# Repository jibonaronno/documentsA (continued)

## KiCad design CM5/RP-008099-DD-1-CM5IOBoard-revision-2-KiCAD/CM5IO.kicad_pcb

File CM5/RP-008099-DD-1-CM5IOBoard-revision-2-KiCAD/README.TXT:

These files have been created in version 9 of KiCAD.

Some of the 3d models need to be downloaded form the following places and put into the CM5IO.3shapes directory some models are approximations.

https://datasheets.raspberrypi.org/cm5/CM5-step.zip
https://www.molex.com/molex/products/part-detail/memory_card_socket/5033981892

The models provided in the 3dmodels directory are from various manufacturers including Diodes, Hirose, MTCONN, Toby, TRXCOM. Terms and conditions for the use of the models remain with the original manufacture.

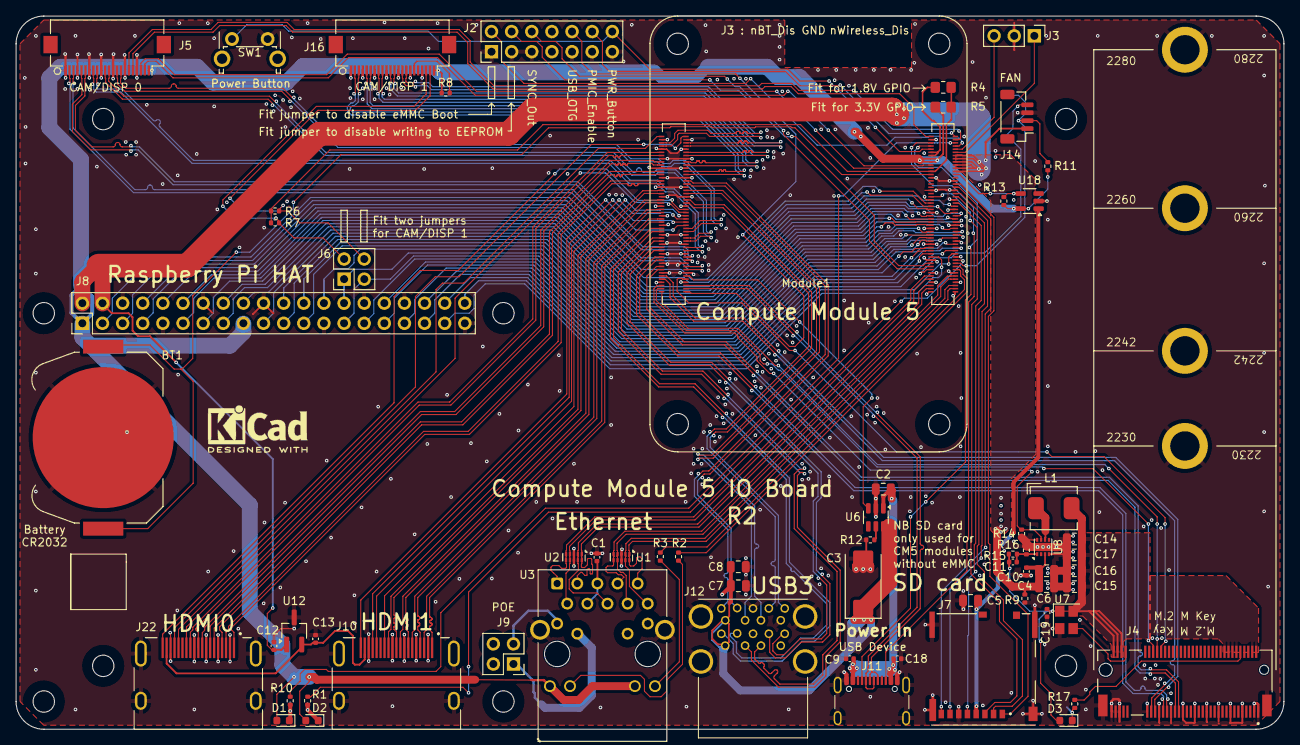
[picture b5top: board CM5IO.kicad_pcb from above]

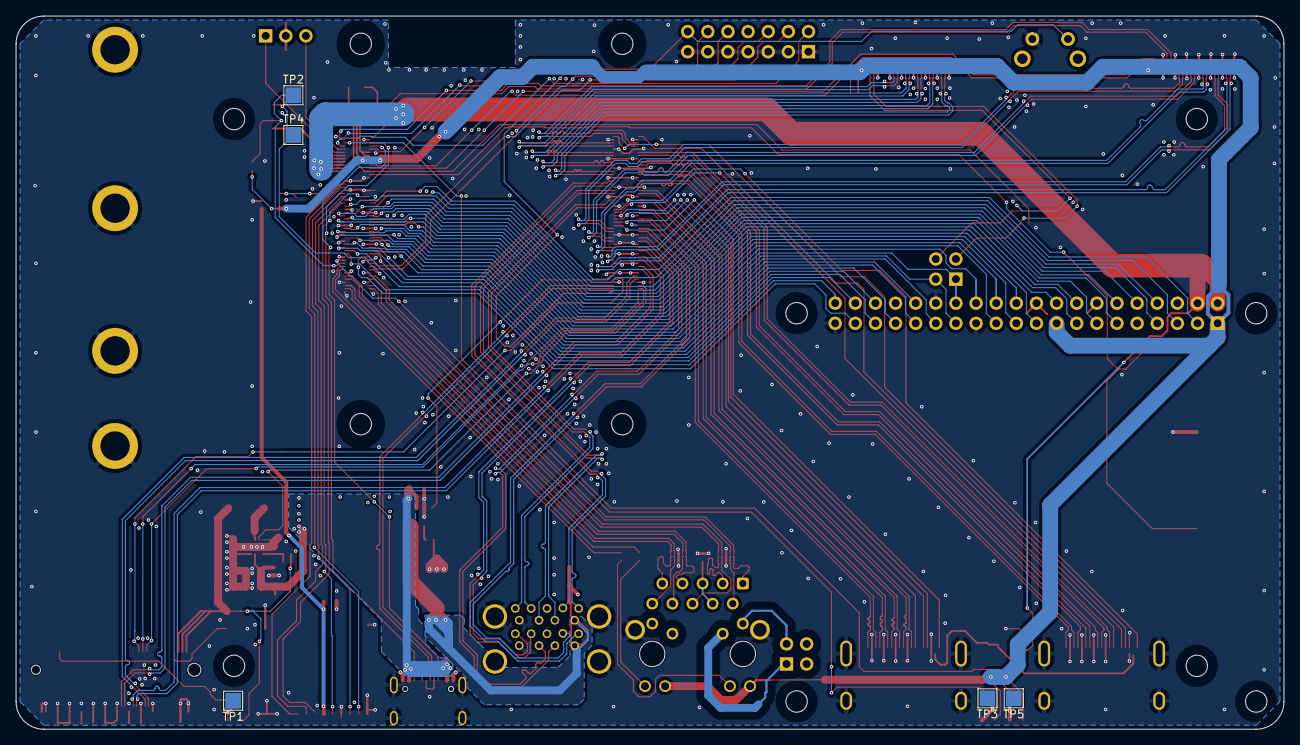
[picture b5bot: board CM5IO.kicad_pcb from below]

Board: 4 copper layers, 160.0 x 90.0 mm, 78 parts (5 on the bottom side), 160 nets.

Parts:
BT1: Battery_Cell; BatteryHolder_Keystone_3034_1x20mm
C1, C9, C10, C12, C13, C18, C19: 100n; C_0402_1005Metric
C2, C4, C5, C6, C7, C8, C14, C15, C16, C17: 10u; C_0805_2012Metric
C3: 100uF; CP_EIA-7343-31_Kemet-D
C11: 4.7nF; C_0402_1005Metric
D1: LED Red; LED_0603_1608Metric
D2, D3: LED Green; LED_0603_1608Metric
H1, H2, H3, H4, H5, H6, H7, H8: MountingHole; MountingHole_2.7mm_M2.5_DIN965
J2: Conn_02x07_Odd_Even; PinHeader_2x07_P2.54mm_Vertical
J3: Conn_01x03; PinHeader_1x03_P2.54mm_Vertical
J4: Bus_M.2_Socket_M; M.2 M Key socket
J5, J16: Conn_01x22_Female; Hirose_FH12-22S-0.5SH_1x22-1MP_P0.50mm_Horizontal
J6, J9: THD-02-R; PinHeader_2x02_P2.54mm_Vertical
J7: Micro_SD_Card_Det; SDCARD_MOLEX_503398-1892
J8: THD-20-R; PinHeader_2x20_P2.54mm_Vertical
J10, J22: 690-019-298-412; EDAC 690-019-298-412
J11: USB_C_Receptacle_USB2.0; USB_C_Receptacle_GCT_USB4105-xx-A_16P_TopMnt_Horizontal
J12: USB3_A; MTCONN_UBAF30-D2011
J14: JST_SHBM04B-SRSS-TB; JST_SH_BM04B-SRSS-TB_1x04-1MP_P1.00mm_Vertical
L1: 2.2uH; L_Bourns_SRP5030CC
Module1: ComputeModule5-CM5; Raspberry-Pi-5-Compute-Module
R1, R10, R17: 1k; R_0402_1005Metric
R2, R3: 470R; R_0402_1005Metric
R4: nf; R_0805_2012Metric_Pad1.20x1.40mm_HandSolder
R5: 0R; R_0805_2012Metric_Pad1.20x1.40mm_HandSolder
R6, R7, R8, R9, R16: 2.2K 1%; R_0402_1005Metric
R11, R13, R15: 10K 1%; R_0402_1005Metric
R12: 15K 1%; R_0402_1005Metric
R14: 100K 1%; R_0402_1005Metric
SW1: Right angle Tact button; SW_Tactile_SPST_Angled_PTS645Vx58-2LFS
TP1, TP2, TP3, TP4, TP5: TestPoint; TestPoint_Pad_2.0x2.0mm
U1, U2: TPD4EUSB30; USON-10_2.5x1.0mm_P0.5mm
U3: MagJack-A70-112-331N126; TRJG0926HENL
U6: AP22653W6; SOT-23-6
U7: ASEK-32.768KHZ-L-R-T; Crystal_SMD_3225-4Pin_3.2x2.5mm
U8: AP3441SHE-7B; DFN-8-1EP_2x2mm_P0.5mm_EP1.05x1.75mm
U12: RT9742SNGV; TSOT-23_HandSoldering
U18: RT9742GGJ5; SOT-23-5

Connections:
/+3.3v: D1.2 (A), D2.2 (A), J5.22, J8.1, J8.17, J16.22, Module1.84 (+3.3v_(Output)), Module1.86 (+3.3v_(Output)), R5.1, R8.1, R11.1, R13.1, U3.15 (LEDY_A), U3.17 (LEDG_A), U18.5 (IN)
/+5v: C2.1, C4.1, C6.1, C9.1, C10.1, C12.1, C18.1, J8.2, J8.4, J11.A4 (VBUS), J11.A9 (VBUS), J11.B4 (VBUS), J11.B9 (VBUS), J14.1, Module1.77 (+5v_(Input)), Module1.79 (+5v_(Input)), Module1.81 (+5v_(Input)), Module1.83 (+5v_(Input)), Module1.85 (+5v_(Input)), Module1.87 (+5v_(Input)), R9.1, U6.1 (IN), U8.3 (VIN), U12.1 (IN)
/CC1: J11.A5 (CC1), Module1.94 (CC1)
/CC2: J11.B5 (CC2), Module1.96 (CC2)
/CM5_GPIO ( Ethernet, GPIO, SDCARD)/+1.8v: Module1.88 (+1.8v_(Output)), Module1.90 (+1.8v_(Output)), R4.1
/CM5_GPIO ( Ethernet, GPIO, SDCARD)/BT_nDis: J3.3, Module1.91 (BT_nDisable)
/CM5_GPIO ( Ethernet, GPIO, SDCARD)/CAM_GPIO0: J5.17, Module1.97 (CAM_GPIO0)
/CM5_GPIO ( Ethernet, GPIO, SDCARD)/CAM_GPIO1: J5.18, Module1.100 (CAM_GPIO1)
/CM5_GPIO ( Ethernet, GPIO, SDCARD)/EEPROM_nWP: J2.4, Module1.20 (EEPROM_nWP)
/CM5_GPIO ( Ethernet, GPIO, SDCARD)/ETH_LEDG: Module1.17 (Ethernet_nLED2(3.3v)), R2.2
/CM5_GPIO ( Ethernet, GPIO, SDCARD)/ETH_LEDY: Module1.15 (Ethernet_nLED3(3.3v)), R3.2
/CM5_GPIO ( Ethernet, GPIO, SDCARD)/GPIO2: J8.3, Module1.58 (GPIO2)
/CM5_GPIO ( Ethernet, GPIO, SDCARD)/GPIO3: J8.5, Module1.56 (GPIO3)
/CM5_GPIO ( Ethernet, GPIO, SDCARD)/GPIO4: J8.7, Module1.54 (GPIO4)
/CM5_GPIO ( Ethernet, GPIO, SDCARD)/GPIO5: J8.29, Module1.34 (GPIO5)
/CM5_GPIO ( Ethernet, GPIO, SDCARD)/GPIO6: J8.31, Module1.30 (GPIO6)
/CM5_GPIO ( Ethernet, GPIO, SDCARD)/GPIO7: J8.26, Module1.37 (GPIO7)
/CM5_GPIO ( Ethernet, GPIO, SDCARD)/GPIO8: J8.24, Module1.39 (GPIO8)
/CM5_GPIO ( Ethernet, GPIO, SDCARD)/GPIO9: J8.21, Module1.40 (GPIO9)
/CM5_GPIO ( Ethernet, GPIO, SDCARD)/GPIO10: J8.19, Module1.44 (GPIO10)
/CM5_GPIO ( Ethernet, GPIO, SDCARD)/GPIO11: J8.23, Module1.38 (GPIO11)
/CM5_GPIO ( Ethernet, GPIO, SDCARD)/GPIO12: J8.32, Module1.31 (GPIO12)
/CM5_GPIO ( Ethernet, GPIO, SDCARD)/GPIO13: J8.33, Module1.28 (GPIO13)
/CM5_GPIO ( Ethernet, GPIO, SDCARD)/GPIO14: J8.8, Module1.55 (GPIO14)
/CM5_GPIO ( Ethernet, GPIO, SDCARD)/GPIO15: J8.10, Module1.51 (GPIO15)
/CM5_GPIO ( Ethernet, GPIO, SDCARD)/GPIO16: J8.36, Module1.29 (GPIO16)
/CM5_GPIO ( Ethernet, GPIO, SDCARD)/GPIO17: J8.11, Module1.50 (GPIO17)
/CM5_GPIO ( Ethernet, GPIO, SDCARD)/GPIO18: J8.12, Module1.49 (GPIO18)
/CM5_GPIO ( Ethernet, GPIO, SDCARD)/GPIO19: J8.35, Module1.26 (GPIO19)
/CM5_GPIO ( Ethernet, GPIO, SDCARD)/GPIO20: J8.38, Module1.27 (GPIO20)
/CM5_GPIO ( Ethernet, GPIO, SDCARD)/GPIO21: J8.40, Module1.25 (GPIO21)
/CM5_GPIO ( Ethernet, GPIO, SDCARD)/GPIO22: J8.15, Module1.46 (GPIO22)
/CM5_GPIO ( Ethernet, GPIO, SDCARD)/GPIO23: J8.16, Module1.47 (GPIO23)
/CM5_GPIO ( Ethernet, GPIO, SDCARD)/GPIO24: J8.18, Module1.45 (GPIO24)
/CM5_GPIO ( Ethernet, GPIO, SDCARD)/GPIO25: J8.22, Module1.41 (GPIO25)
/CM5_GPIO ( Ethernet, GPIO, SDCARD)/GPIO26: J8.37, Module1.24 (GPIO26)
/CM5_GPIO ( Ethernet, GPIO, SDCARD)/GPIO27: J8.13, Module1.48 (GPIO27)
/CM5_GPIO ( Ethernet, GPIO, SDCARD)/GPIO_VREF: Module1.78 (GPIO_VREF(1.8v/3.3v_Input)), R4.2, R5.2, R6.1, R7.1
/CM5_GPIO ( Ethernet, GPIO, SDCARD)/ID_SC: J6.1, J8.28, Module1.35 (ID_SC)
/CM5_GPIO ( Ethernet, GPIO, SDCARD)/ID_SD: J6.3, J8.27, Module1.36 (ID_SD)
/CM5_GPIO ( Ethernet, GPIO, SDCARD)/PMIC_ENABLE: J2.12, Module1.99 (PMIC_ENABLE)
/CM5_GPIO ( Ethernet, GPIO, SDCARD)/PWM: J14.2, Module1.19 (FAN_PWM), R11.2, TP2.1
/CM5_GPIO ( Ethernet, GPIO, SDCARD)/PWR_BUT: J2.14, Module1.92 (PWR_BUT), SW1.1
/CM5_GPIO ( Ethernet, GPIO, SDCARD)/SD_CLK: J7.5 (CLK), Module1.57 (SD_CLK)
/CM5_GPIO ( Ethernet, GPIO, SDCARD)/SD_CMD: J7.3 (CMD), Module1.62 (SD_CMD)
/CM5_GPIO ( Ethernet, GPIO, SDCARD)/SD_DAT0: J7.7 (DAT0), Module1.63 (SD_DAT0)
/CM5_GPIO ( Ethernet, GPIO, SDCARD)/SD_DAT1: J7.8 (DAT1), Module1.67 (SD_DAT1)
/CM5_GPIO ( Ethernet, GPIO, SDCARD)/SD_DAT2: J7.1 (DAT2), Module1.69 (SD_DAT2)
/CM5_GPIO ( Ethernet, GPIO, SDCARD)/SD_DAT3: J7.2 (DAT3/CD), Module1.61 (SD_DAT3)
/CM5_GPIO ( Ethernet, GPIO, SDCARD)/SD_PWR: C5.1, J7.4 (VDD), U18.1 (OUT)
/CM5_GPIO ( Ethernet, GPIO, SDCARD)/SD_PWR_ON: Module1.75 (SD_PWR_ON), R13.2, U18.4 (EN)
/CM5_GPIO ( Ethernet, GPIO, SDCARD)/SYNC_OUT: J2.6, Module1.18 (Ethernet_SYNC_OUT(3.3v))
/CM5_GPIO ( Ethernet, GPIO, SDCARD)/TACHO: J14.4, Module1.16 (FAN_TACHO), TP4.1
/CM5_GPIO ( Ethernet, GPIO, SDCARD)/TR0_TAP: J9.3, U3.11 (VC1)
/CM5_GPIO ( Ethernet, GPIO, SDCARD)/TR1_TAP: J9.1, U3.12 (VC2)
/CM5_GPIO ( Ethernet, GPIO, SDCARD)/TR2_TAP: J9.2, U3.13 (VC3)
/CM5_GPIO ( Ethernet, GPIO, SDCARD)/TR3_TAP: J9.4, U3.14 (VC4)
/CM5_GPIO ( Ethernet, GPIO, SDCARD)/TRD0_N: Module1.10 (Ethernet_Pair0_N), U2.4 (D2+), U2.7, U3.2 (TRD0-)
/CM5_GPIO ( Ethernet, GPIO, SDCARD)/TRD0_P: Module1.12 (Ethernet_Pair0_P), U2.5 (D2-), U2.6, U3.1 (TRD0+)
/CM5_GPIO ( Ethernet, GPIO, SDCARD)/TRD1_N: Module1.6 (Ethernet_Pair1_N), U2.2 (D1-), U2.9, U3.6 (TRD1-)
/CM5_GPIO ( Ethernet, GPIO, SDCARD)/TRD1_P: Module1.4 (Ethernet_Pair1_P), U2.1 (D1+), U2.10, U3.3 (TRD1+)
/CM5_GPIO ( Ethernet, GPIO, SDCARD)/TRD2_N: Module1.9 (Ethernet_Pair2_N), U1.4 (D2+), U1.7, U3.8 (TRD2-)
/CM5_GPIO ( Ethernet, GPIO, SDCARD)/TRD2_P: Module1.11 (Ethernet_Pair2_P), U1.5 (D2-), U1.6, U3.7 (TRD2+)
/CM5_GPIO ( Ethernet, GPIO, SDCARD)/TRD3_N: Module1.5 (Ethernet_Pair3_N), U1.2 (D1-), U1.9, U3.10 (TRD3-)
/CM5_GPIO ( Ethernet, GPIO, SDCARD)/TRD3_P: Module1.3 (Ethernet_Pair3_P), U1.1 (D1+), U1.10, U3.9 (TRD3+)
/CM5_GPIO ( Ethernet, GPIO, SDCARD)/USBOTG: J2.10, Module1.101 (USB_OTG_ID)
/CM5_GPIO ( Ethernet, GPIO, SDCARD)/VBAT: BT1.1 (+), Module1.76 (VBAT)
/CM5_GPIO ( Ethernet, GPIO, SDCARD)/WL_nDis: J3.1, Module1.89 (WiFi_nDisable)
/CM5_GPIO ( Ethernet, GPIO, SDCARD)/nPWR_LED: Module1.95 (LED_nPWR), R10.2
/CM5_GPIO ( Ethernet, GPIO, SDCARD)/nRPIBOOT: J2.2, Module1.93 (nRPIBOOT)
/CM5_HighSpeed/DPHY0_C_N: J5.8, Module1.127 (MIPI0_C_N)
/CM5_HighSpeed/DPHY0_C_P: J5.9, Module1.129 (MIPI0_C_P)
/CM5_HighSpeed/DPHY0_D0_N: J5.2, Module1.115 (MIPI0_D0_N)
/CM5_HighSpeed/DPHY0_D0_P: J5.3, Module1.117 (MIPI0_D0_P)
/CM5_HighSpeed/DPHY0_D1_N: J5.5, Module1.121 (MIPI0_D1_N)
/CM5_HighSpeed/DPHY0_D1_P: J5.6, Module1.123 (MIPI0_D1_P)
/CM5_HighSpeed/DPHY0_D2_N: J5.11, Module1.133 (MIPI0_D2_N)
/CM5_HighSpeed/DPHY0_D2_P: J5.12, Module1.135 (MIPI0_D2_P)
/CM5_HighSpeed/DPHY0_D3_N: J5.14, Module1.139 (MIPI0_D3_N)
/CM5_HighSpeed/DPHY0_D3_P: J5.15, Module1.141 (MIPI0_D3_P)
/CM5_HighSpeed/DPHY1_C_N: J16.8, Module1.187 (MIPI1_C_N)
/CM5_HighSpeed/DPHY1_C_P: J16.9, Module1.189 (MIPI1_C_P)
/CM5_HighSpeed/DPHY1_D0_N: J16.2, Module1.175 (MIPI1_D0_N)
/CM5_HighSpeed/DPHY1_D0_P: J16.3, Module1.177 (MIPI1_D0_P)
/CM5_HighSpeed/DPHY1_D1_N: J16.5, Module1.181 (MIPI1_D1_N)
/CM5_HighSpeed/DPHY1_D1_P: J16.6, Module1.183 (MIPI1_D1_P)
/CM5_HighSpeed/DPHY1_D2_N: J16.11, Module1.193 (MIPI1_D2_N)
/CM5_HighSpeed/DPHY1_D2_P: J16.12, Module1.195 (MIPI1_D2_P)
/CM5_HighSpeed/DPHY1_D3_N: J16.14, Module1.194 (MIPI1_D3_N)
/CM5_HighSpeed/DPHY1_D3_P: J16.15, Module1.196 (MIPI1_D3_P)
/CM5_HighSpeed/HDMI0_CEC: J22.13 (CEC), Module1.151 (HDMI0_CEC)
/CM5_HighSpeed/HDMI0_CK_N: J22.12 (CK-), Module1.190 (HDMI0_CLK_N)
/CM5_HighSpeed/HDMI0_CK_P: J22.10 (CK+), Module1.188 (HDMI0_CLK_P)
/CM5_HighSpeed/HDMI0_D0_N: J22.9 (D0-), Module1.184 (HDMI0_TX0_N)
/CM5_HighSpeed/HDMI0_D0_P: J22.7 (D0+), Module1.182 (HDMI0_TX0_P)
/CM5_HighSpeed/HDMI0_D1_N: J22.6 (D1-), Module1.178 (HDMI0_TX1_N)
/CM5_HighSpeed/HDMI0_D1_P: J22.4 (D1+), Module1.176 (HDMI0_TX1_P)
/CM5_HighSpeed/HDMI0_D2_N: J22.3 (D2-), Module1.172 (HDMI0_TX2_N)
/CM5_HighSpeed/HDMI0_D2_P: J22.1 (D2+), Module1.170 (HDMI0_TX2_P)
/CM5_HighSpeed/HDMI0_HOTPLUG: J22.19 (HPD/HEAC-), Module1.153 (HDMI0_HOTPLUG)
/CM5_HighSpeed/HDMI0_SCL: J22.15 (SCL), Module1.200 (HDMI0_SCL)
/CM5_HighSpeed/HDMI0_SDA: J22.16 (SDA), Module1.199 (HDMI0_SDA)
/CM5_HighSpeed/HDMI1_CEC: J10.13 (CEC), Module1.149 (HDMI1_CEC)
/CM5_HighSpeed/HDMI1_CK_N: J10.12 (CK-), Module1.166 (HDMI1_CLK_N)
/CM5_HighSpeed/HDMI1_CK_P: J10.10 (CK+), Module1.164 (HDMI1_CLK_P)
/CM5_HighSpeed/HDMI1_D0_N: J10.9 (D0-), Module1.160 (HDMI1_TX0_N)
/CM5_HighSpeed/HDMI1_D0_P: J10.7 (D0+), Module1.158 (HDMI1_TX0_P)
/CM5_HighSpeed/HDMI1_D1_N: J10.6 (D1-), Module1.154 (HDMI1_TX1_N)
/CM5_HighSpeed/HDMI1_D1_P: J10.4 (D1+), Module1.152 (HDMI1_TX1_P)
/CM5_HighSpeed/HDMI1_D2_N: J10.3 (D2-), Module1.148 (HDMI1_TX2_N)
/CM5_HighSpeed/HDMI1_D2_P: J10.1 (D2+), Module1.146 (HDMI1_TX2_P)
/CM5_HighSpeed/HDMI1_HOTPLUG: J10.19 (HPD/HEAC-), Module1.143 (HDMI1_HOTPLUG)
/CM5_HighSpeed/HDMI1_SCL: J10.15 (SCL), Module1.147 (HDMI1_SCL)
/CM5_HighSpeed/HDMI1_SDA: J10.16 (SDA), Module1.145 (HDMI1_SDA)
/CM5_HighSpeed/HDMI_5v: C13.1, J10.18 (+5V), J22.18 (+5V), U12.2 (OUT)
/CM5_HighSpeed/PCIE_CLK_N: J4.53 (REFCLKn), Module1.112 (PCIe_CLK_N)
/CM5_HighSpeed/PCIE_CLK_P: J4.55 (REFCLKp), Module1.110 (PCIe_CLK_P)
/CM5_HighSpeed/PCIE_PWR_EN: Module1.106 (PCIE_PWR_EN), R14.1, U8.7 (EN)
/CM5_HighSpeed/PCIE_RX_N: J4.43 (PETp0), Module1.118 (PCIe_RX_N)
/CM5_HighSpeed/PCIE_RX_P: J4.41 (PETn0), Module1.116 (PCIe_RX_P)
/CM5_HighSpeed/PCIE_TX_N: J4.49 (PERp0), Module1.124 (PCIe_TX_N)
/CM5_HighSpeed/PCIE_TX_P: J4.47 (PERn0), Module1.122 (PCIe_TX_P)
/CM5_HighSpeed/PCIE_nCLKREQ: J4.52 (~CLKREQ), Module1.102 (PCIe_nCLKREQ)
/CM5_HighSpeed/PCIE_nRST: J4.50 (~PERST), Module1.109 (PCIe_nRST)
/CM5_HighSpeed/PCIE_nWAKE: J4.54 (~PEWAKE), Module1.104 (PCIE_nWAKE)
/CM5_HighSpeed/SCL0: J5.20, Module1.80 (SCL0)
/CM5_HighSpeed/SCL1: J6.2, J16.20, R7.2
/CM5_HighSpeed/SDA0: J5.21, Module1.82 (SDA0)
/CM5_HighSpeed/SDA1: J6.4, J16.21, R6.2
/CM5_HighSpeed/USB3-0-D_N: J12.A2 (D-), Module1.136 (USB3-0-D_N)
/CM5_HighSpeed/USB3-0-D_P: J12.A3 (D+), Module1.134 (USB3-0-D_P)
/CM5_HighSpeed/USB3-0-RX_N: J12.A6 (SSRX+), Module1.128 (USB3-0-RX_N)
/CM5_HighSpeed/USB3-0-RX_P: J12.A5 (SSRX-), Module1.130 (USB3-0-RX_P)
/CM5_HighSpeed/USB3-0-TX_N: J12.A9 (SSTX+), Module1.140 (USB3-0-TX_N)
/CM5_HighSpeed/USB3-0-TX_P: J12.A8 (SSTX-), Module1.142 (USB3-0-TX_P)
/CM5_HighSpeed/USB3-1-D_N: J12.B2 (D-), Module1.165 (USB3-1-D_N)
/CM5_HighSpeed/USB3-1-D_P: J12.B3 (D+), Module1.163 (USB3-1-D_P)
/CM5_HighSpeed/USB3-1-RX_N: J12.B6 (SSRX+), Module1.157 (USB3-1-RX_N)
/CM5_HighSpeed/USB3-1-RX_P: J12.B5 (SSRX-), Module1.159 (USB3-1-RX_P)
/CM5_HighSpeed/USB3-1-TX_N: J12.B9 (SSTX+), Module1.169 (USB3-1-TX_N)
/CM5_HighSpeed/USB3-1-TX_P: J12.B8 (SSTX-), Module1.171 (USB3-1-TX_P)
/CM5_HighSpeed/VBUS: C3.1, C7.1, C8.1, J12.A1 (VBUS), J12.B1 (VBUS), U6.6 (OUT)
/CM5_HighSpeed/VBUS_EN: Module1.111 (VBUS_EN), U6.3 (EN)
/PCIe-M2/FB: C11.2, R15.2, R16.1, U8.1 (FB)
/PCIe-M2/M2_3v3: C11.1, C14.1, C15.1, C16.1, C17.1, C19.1, D3.2 (A), J4.2 (3.3V), J4.4 (3.3V), J4.12 (3.3V), J4.14 (3.3V), J4.16 (3.3V), J4.18 (3.3V), J4.70 (3.3V), J4.72 (3.3V), J4.74 (3.3V), L1.2, R15.1, U7.1 (EN), U7.4 (VDD)
/USB2_N: J11.A7 (D-), J11.B7 (D-), Module1.103 (USB2_N)
/USB2_P: J11.A6 (D+), J11.B6 (D+), Module1.105 (USB2_P)
GND: BT1.2 (-), C1.2, C2.2, C3.2, C4.2, C5.2, C6.2, C7.2, C8.2, C9.2, C10.2, C12.2, C13.2, C14.2, C15.2, C16.2, C17.2, C18.2, C19.2, J2.1, J2.3, J2.5, J2.7, J2.9, J2.11, J2.13, J3.2, J4.1 (GND), J4.3 (GND), J4.9 (GND), J4.15 (GND), J4.21 (GND), J4.27 (GND), J4.33 (GND), J4.39 (GND), J4.45 (GND), J4.51 (GND), J4.57 (GND), J4.71 (GND), J4.73 (GND), J4.75 (GND), J4.M1 (GND2230), J4.M2 (GND2242), J4.M3 (GND2260), J4.M4 (GND2280), J4.S1, J4.S2, J5.1, J5.4, J5.7, J5.10, J5.13, J5.16, J5.19, J7.6 (VSS), J7.11 (SHIELD), J8.6, J8.9, J8.14, J8.20, J8.25, J8.30, J8.34, J8.39, J10.2 (D2S), J10.5 (D1S), J10.8 (D0S), J10.11 (CKS), J10.17 (GND), J10.SH1 (SH), J10.SH2 (SH), J10.SH3 (SH), J10.SH4 (SH), J11.A1 (GND), J11.A12 (GND), J11.B1 (GND), J11.B12 (GND), J11.S1 (SHIELD), J12.10 (SHIELD), J12.A4 (GND), J12.A7 (DRAIN), J12.B4 (GND), J12.B7 (DRAIN), J14.3, J16.1, J16.4, J16.7, J16.10, J16.13, J16.16, J16.19, J22.2 (D2S), J22.5 (D1S), J22.8 (D0S), J22.11 (CKS), J22.17 (GND), J22.SH1 (SH), J22.SH2 (SH), J22.SH3 (SH), J22.SH4 (SH), Module1.1 (GND), Module1.2 (GND), Module1.7 (GND), Module1.8 (GND), Module1.13 (GND), Module1.14 (GND), Module1.22 (GND), Module1.23 (GND), Module1.32 (GND), Module1.33 (GND), Module1.42 (GND), Module1.43 (GND), Module1.52 (GND), Module1.53 (GND), Module1.59 (GND), Module1.60 (GND), Module1.65 (GND), Module1.66 (GND), Module1.71 (GND), Module1.74 (GND), Module1.98 (GND), Module1.107 (GND), Module1.108 (GND), Module1.113 (GND), Module1.114 (GND), Module1.119 (GND), Module1.120 (GND), Module1.125 (GND), Module1.126 (GND), Module1.131 (GND), Module1.132 (GND), Module1.137 (GND), Module1.138 (GND), Module1.144 (GND), Module1.150 (GND), Module1.155 (GND), Module1.156 (GND), Module1.161 (GND), Module1.162 (GND), Module1.167 (GND), Module1.168 (GND), Module1.173 (GND), Module1.174 (GND), Module1.179 (GND), Module1.180 (GND), Module1.185 (GND), Module1.186 (GND), Module1.191 (GND), Module1.192 (GND), Module1.197 (GND), Module1.198 (GND), R9.2, R12.2, R14.2, R16.2, SW1.2, U1.3 (GND), U1.8 (GND), U2.3 (GND), U2.8 (GND), U3.19 (SHIELD), U3.20 (SHIELD), U6.2 (GND), U7.2 (GND), U8.4 (PGND), U8.8 (SGND), U8.9 (PAD), U12.3 (GND), U18.2 (GND)
unnamed: C1.1, U3.4 (CT), U3.5 (CT)
unnamed: D1.1 (K), R10.1, TP5.1
unnamed: D2.1 (K), R1.1, TP3.1
unnamed: D3.1 (K), R17.1, TP1.1
unnamed: J4.10 (DAS/~DSS/~LED1), R17.2
unnamed: J4.68 (SUSCLK), U7.3 (Out)
unnamed: J16.17, R8.2
unnamed: Module1.21 (LED_nACT), R1.2
unnamed: R3.1, U3.18 (LEDG_K)
unnamed: R2.1, U3.16 (LEDY_K)
unnamed: R12.1, U6.5 (ILIM)
unnamed: L1.1, U8.6 (LX)

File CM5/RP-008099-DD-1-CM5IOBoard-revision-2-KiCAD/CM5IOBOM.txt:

"Id";"Designator";"Footprint";"Quantity";"Designation";"Supplier and ref";
1;"BT1";"BatteryHolder_Keystone_3034_1x20mm";1;"Battery_Cell";;;
2;"SW1";"SW_Tactile_SPST_Angled_PTS645Vx39-2LFS";1;"Right angle Tact button";;;
3;"C1,C12,C13,C10,C18,C9,C19";"C_0402_1005Metric";7;"100n";;;
4;"C5,C6,C16,C8,C2,C17,C7,C15,C14,C4";"C_0805_2012Metric";10;"10u";;;
5;"J5,J16";"Hirose_FH12-22S-0.5SH_1x22-1MP_P0.50mm_Horizontal";2;"Conn_01x22_Female";;;
6;"R10,R1,R17";"R_0402_1005Metric";3;"1k";;;
7;"U1,U2";"USON-10_2.5x1.0mm_P0.5mm";2;"TPD4EUSB30";;;
8;"U12";"TSOT-23_HandSoldering";1;"RT9742SNGV";;;
9;"J8";"PinHeader_2x20_P2.54mm_Vertical";1;"THD-20-R";;;
10;"D2,D3";"LED_0603_1608Metric";2;"LED Green";;;
11;"R3,R2";"R_0402_1005Metric";2;"470R";;;
12;"J9,J6";"PinHeader_2x02_P2.54mm_Vertical";2;"THD-02-R";;;
13;"J11";"USB_C_Receptacle_GCT_USB4105-xx-A_16P_TopMnt_Horizontal";1;"USB_C_Receptacle_USB2.0";;;
14;"D1";"LED_0603_1608Metric";1;"LED Red";;;
15;"U5";"SOT-353_SC-70-5";1;"74LVC1G07SE-7";;;
16;"U18";"SOT-23-5";1;"RT9742GGJ5";;;
17;"U3";"TRJG0926HENL";1;"MagJack-A70-112-331N126";;;
18;"J10,J22";"EDAC 690-019-298-412";2;"690-019-298-412";;;
19;"R6,R7,R8,R16";"R_0402_1005Metric";4;"2.2K 1%";;;
20;"J2";"PinHeader_2x07_P2.54mm_Vertical";1;"Conn_02x07_Odd_Even";;;
21;"R5";"R_0805_2012Metric_Pad1.20x1.40mm_HandSolder";1;"0R";;;
22;"U8";"DFN-8-1EP_2x2mm_P0.5mm_EP1.05x1.75mm";1;"AP3441SHE-7B";;;
23;"J7";"SDCARD_MOLEX_503398-1892";1;"Micro_SD_Card_Det";;;
24;"J4";"M.2 M Key socket";1;"Bus_M.2_Socket_M";;;
25;"C11";"C_0402_1005Metric";1;"4.7nF";;;
26;"J12";"MTCONN_UBAF30-D2011";1;"USB3_A";;;
27;"J14";"JST_SH_BM04B-SRSS-TB_1x04-1MP_P1.00mm_Vertical";1;"JST_SHBM04B-SRSS-TB";;;
28;"C3";"CP_EIA-7343-31_Kemet-D";1;"100uF";;;
29;"U7";"Crystal_SMD_3225-4Pin_3.2x2.5mm";1;"ASEK-32.768KHZ-L-R-T";;;
30;"U6";"SOT-23-6";1;"AP22653W6";;;
31;"L1";"L_Bourns_SRP5030CC";1;"2.2uH";;;
32;"R15";"R_0402_1005Metric";1;"10K 1%";;;
33;"R12";"R_0402_1005Metric";1;"15K 1%";;;
34;"R14";"R_0402_1005Metric";1;"100K 1%";;;
35;"Module1";"Raspberry-Pi-5-Compute-Module";1;"ComputeModule5-CM5";;;

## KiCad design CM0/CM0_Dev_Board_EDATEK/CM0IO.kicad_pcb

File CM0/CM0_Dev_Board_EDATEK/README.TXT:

These files have been created in version 9 of KiCAD.

Some of the 3d models need to be downloaded form the following places and put into the CM4IO.3dshapes directory some models are approximations.

https://www.molex.com/molex/products/part-detail/memory_card_socket/5033981892
https://www.molex.com/en-us/products/part-detail/2086581051

The models provided in the 3dmodels directory are from various manufacturers including RaspberryPi, Hirose. Terms and conditions for the use of the models remain with the original manufacture.

The CM0 model has the following license :

= Disclaimer =
These 3D models are provided under the MIT license included at the end of this file. The 3D models may incorporate individual 3D models that have been provided by third parties with permission to redistribute. No additional license terms are imposed by this use of third party provided 3D models, where applicable.

The overall 3D model and any individual 3D models incorporated into the whole, whether created by first or a third party, are provided here for guidance only and without guarantee of accuracy. Additionally, provided 3D model data may not reflect the most current version(s). Any third party intending to use the provided 3D model for appearance and fitment purposes must refer to manufacturer information and conduct suitable measurements of the physical product.

= MIT License =
Copyright (c) 2025 Raspberry Pi Ltd

Permission is hereby granted, free of charge, to any person obtaining a copy of this software and associated documentation files (the "Software"), to deal in the Software without restriction, including without limitation the rights to use, copy, modify, merge, publish, distribute, sublicense, and/or sell copies of the Software, and to permit persons to whom the Software is furnished to do so, subject to the following conditions:

The above copyright notice and this permission notice shall be included in all copies or substantial portions of the Software.

THE SOFTWARE IS PROVIDED "AS IS", WITHOUT WARRANTY OF ANY KIND, EXPRESS OR IMPLIED, INCLUDING BUT NOT LIMITED TO THE WARRANTIES OF MERCHANTABILITY, FITNESS FOR A PARTICULAR PURPOSE AND NONINFRINGEMENT. IN NO EVENT SHALL THE AUTHORS OR COPYRIGHT HOLDERS BE LIABLE FOR ANY CLAIM, DAMAGES OR OTHER LIABILITY, WHETHER IN AN ACTION OF CONTRACT, TORT OR OTHERWISE, ARISING FROM, OUT OF OR IN CONNECTION WITH THE SOFTWARE OR THE USE OR OTHER DEALINGS IN THE SOFTWARE.

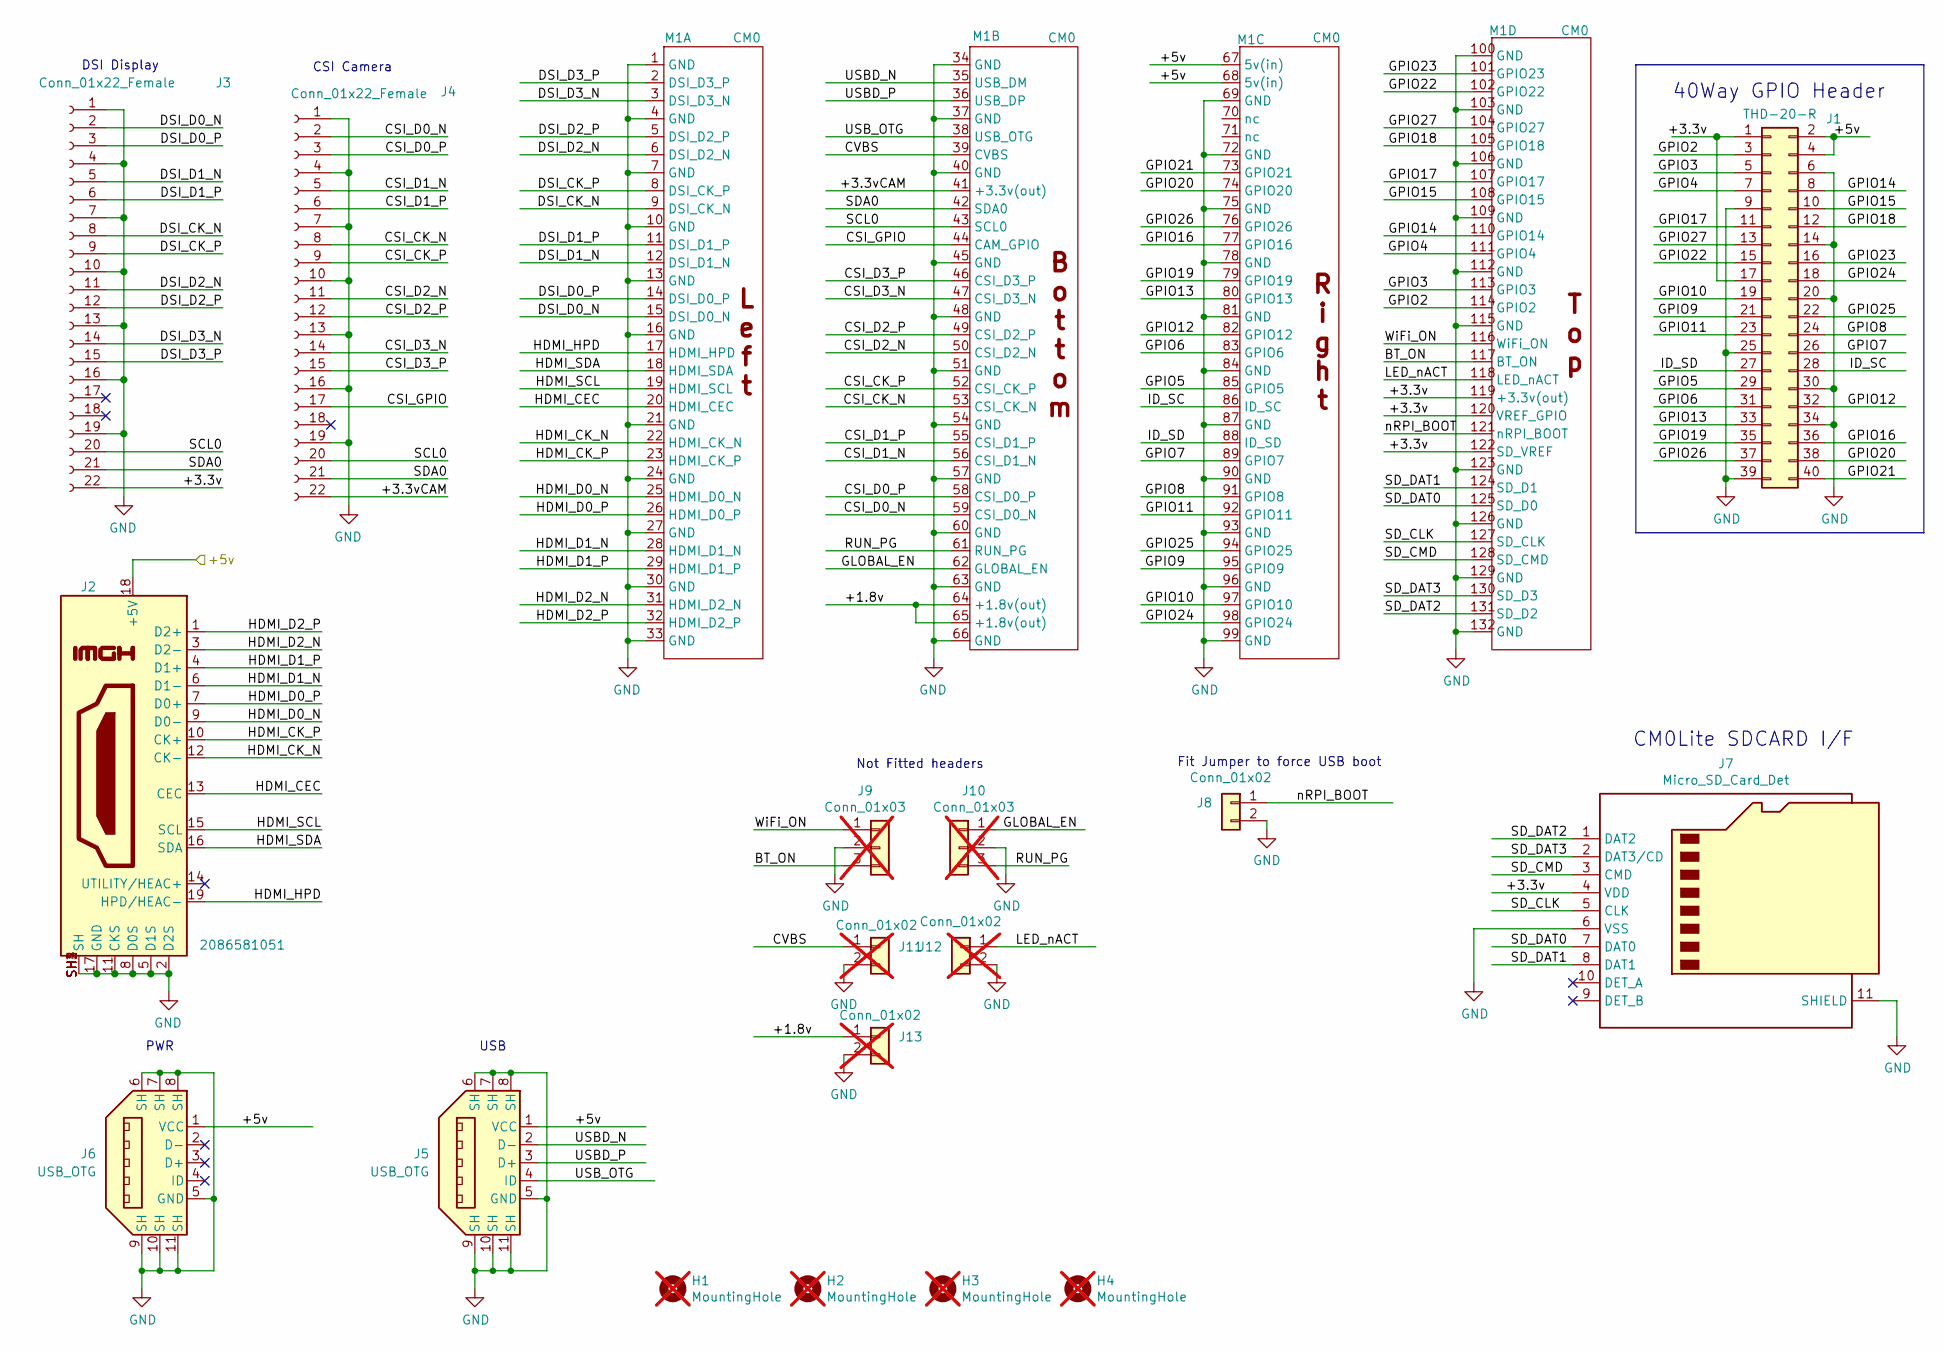
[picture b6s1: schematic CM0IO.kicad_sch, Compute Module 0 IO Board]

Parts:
H1, H2, H3, H4: MountingHole; MountingHole_2.7mm_M2.5; Part Description M2.5 mounting hole; not fitted
J1: THD-20-R; PinHeader_2x20_P2.54mm_Vertical; Part Description PinHeader_2x20_P2.54mm_Vertical
J2: 2086581051; Molex_2086581051; Part Description HDMI Connector, Right Angle, 19 Contact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
J3, J4: Conn_01x22_Female; Hirose_FH12-22S-0.5SH_1x22-1MP_P0.50mm_Horizontal; Part Description 22 Position FFC, FPC Connector Contacts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
J5, J6: USB_OTG; amphenol_10103594-0001lf; Part Description USB - micro B USB 2.0 Receptacle Connec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
J7: Micro_SD_Card_Det; SDCARD_MOLEX_503398-1892; Part Description 9 (8 + 1) Position Card Connector micro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
J8: Conn_01x02; PinHeader_1x02_P2.54mm_Vertical
J9, J10: Conn_01x03; PinHeader_1x03_P2.54mm_Vertical; Part Description 3pin 0.1" connector; not fitted
J11, J12, J13: Conn_01x02; PinHeader_1x02_P2.54mm_Vertical; not fitted
M1: CM0; Part Description Compute Module 0

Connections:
/+1.8v: J13.1, M1.64 (+1.8v(out)), M1.65 (+1.8v(out))
/+3.3v: J1.1, J1.17, J3.22, J7.4 (VDD), M1.119 (+3.3v(out)), M1.120 (VREF_GPIO), M1.122 (SD_VREF)
/+3.3vCAM: J4.22, M1.41 (+3.3v(out))
/+5v: J1.2, J1.4, J2.18 (+5V), J5.1 (VCC), J6.1 (VCC), M1.67 (5v(in)), M1.68 (5v(in))
/BT_ON: J9.3, M1.117 (BT_ON)
/CSI_CK_N: J4.8, M1.53 (CSI_CK_N)
/CSI_CK_P: J4.9, M1.52 (CSI_CK_P)
/CSI_D0_N: J4.2, M1.59 (CSI_D0_N)
/CSI_D0_P: J4.3, M1.58 (CSI_D0_P)
/CSI_D1_N: J4.5, M1.56 (CSI_D1_N)
/CSI_D1_P: J4.6, M1.55 (CSI_D1_P)
/CSI_D2_N: J4.11, M1.50 (CSI_D2_N)
/CSI_D2_P: J4.12, M1.49 (CSI_D2_P)
/CSI_D3_N: J4.14, M1.47 (CSI_D3_N)
/CSI_D3_P: J4.15, M1.46 (CSI_D3_P)
/CSI_GPIO: J4.17, M1.44 (CAM_GPIO)
/CVBS: J11.1, M1.39 (CVBS)
/DSI_CK_N: J3.8, M1.9 (DSI_CK_N)
/DSI_CK_P: J3.9, M1.8 (DSI_CK_P)
/DSI_D0_N: J3.2, M1.15 (DSI_D0_N)
/DSI_D0_P: J3.3, M1.14 (DSI_D0_P)
/DSI_D1_N: J3.5, M1.12 (DSI_D1_N)
/DSI_D1_P: J3.6, M1.11 (DSI_D1_P)
/DSI_D2_N: J3.11, M1.6 (DSI_D2_N)
/DSI_D2_P: J3.12, M1.5 (DSI_D2_P)
/DSI_D3_N: J3.14, M1.3 (DSI_D3_N)
/DSI_D3_P: J3.15, M1.2 (DSI_D3_P)
/GLOBAL_EN: J10.1, M1.62 (GLOBAL_EN)
/GPIO2: J1.3, M1.114 (GPIO2)
/GPIO3: J1.5, M1.113 (GPIO3)
/GPIO4: J1.7, M1.111 (GPIO4)
/GPIO5: J1.29, M1.85 (GPIO5)
/GPIO6: J1.31, M1.83 (GPIO6)
/GPIO7: J1.26, M1.89 (GPIO7)
/GPIO8: J1.24, M1.91 (GPIO8)
/GPIO9: J1.21, M1.95 (GPIO9)
/GPIO10: J1.19, M1.97 (GPIO10)
/GPIO11: J1.23, M1.92 (GPIO11)
/GPIO12: J1.32, M1.82 (GPIO12)
/GPIO13: J1.33, M1.80 (GPIO13)
/GPIO14: J1.8, M1.110 (GPIO14)
/GPIO15: J1.10, M1.108 (GPIO15)
/GPIO16: J1.36, M1.77 (GPIO16)
/GPIO17: J1.11, M1.107 (GPIO17)
/GPIO18: J1.12, M1.105 (GPIO18)
/GPIO19: J1.35, M1.79 (GPIO19)
/GPIO20: J1.38, M1.74 (GPIO20)
/GPIO21: J1.40, M1.73 (GPIO21)
/GPIO22: J1.15, M1.102 (GPIO22)
/GPIO23: J1.16, M1.101 (GPIO23)
/GPIO24: J1.18, M1.98 (GPIO24)
/GPIO25: J1.22, M1.94 (GPIO25)
/GPIO26: J1.37, M1.76 (GPIO26)
/GPIO27: J1.13, M1.104 (GPIO27)
/HDMI_CEC: J2.13 (CEC), M1.20 (HDMI_CEC)
/HDMI_CK_N: J2.12 (CK-), M1.22 (HDMI_CK_N)
/HDMI_CK_P: J2.10 (CK+), M1.23 (HDMI_CK_P)
/HDMI_D0_N: J2.9 (D0-), M1.25 (HDMI_D0_N)
/HDMI_D0_P: J2.7 (D0+), M1.26 (HDMI_D0_P)
/HDMI_D1_N: J2.6 (D1-), M1.28 (HDMI_D1_N)
/HDMI_D1_P: J2.4 (D1+), M1.29 (HDMI_D1_P)
/HDMI_D2_N: J2.3 (D2-), M1.31 (HDMI_D2_N)
/HDMI_D2_P: J2.1 (D2+), M1.32 (HDMI_D2_P)
/HDMI_HPD: J2.19 (HPD/HEAC-), M1.17 (HDMI_HPD)
/HDMI_SCL: J2.15 (SCL), M1.19 (HDMI_SCL)
/HDMI_SDA: J2.16 (SDA), M1.18 (HDMI_SDA)
/ID_SC: J1.28, M1.86 (ID_SC)
/ID_SD: J1.27, M1.88 (ID_SD)
/LED_nACT: J12.1, M1.118 (LED_nACT)
/RUN_PG: J10.3, M1.61 (RUN_PG)
/SCL0: J3.20, J4.20, M1.43 (SCL0)
/SDA0: J3.21, J4.21, M1.42 (SDA0)
/SD_CLK: J7.5 (CLK), M1.127 (SD_CLK)
/SD_CMD: J7.3 (CMD), M1.128 (SD_CMD)
/SD_DAT0: J7.7 (DAT0), M1.125 (SD_D0)
/SD_DAT1: J7.8 (DAT1), M1.124 (SD_D1)
/SD_DAT2: J7.1 (DAT2), M1.131 (SD_D2)
/SD_DAT3: J7.2 (DAT3/CD), M1.130 (SD_D3)
/USBD_N: J5.2 (D-), M1.35 (USB_DM)
/USBD_P: J5.3 (D+), M1.36 (USB_DP)
/USB_OTG: J5.4 (ID), M1.38 (USB_OTG)
/WiFi_ON: J9.1, M1.116 (WiFi_ON)
/nRPI_BOOT: J8.1, M1.121 (nRPI_BOOT)
GND: J1.6, J1.9, J1.14, J1.20, J1.25, J1.30, J1.34, J1.39, J2.2 (D2S), J2.5 (D1S), J2.8 (D0S), J2.11 (CKS), J2.17 (GND), J2.SH1 (SH), J2.SH2 (SH), J2.SH3 (SH), J2.SH4 (SH), J3.1, J3.4, J3.7, J3.10, J3.13, J3.16, J3.19, J4.1, J4.4, J4.7, J4.10, J4.13, J4.16, J4.19, J5.5 (GND), J5.6 (SH), J5.7 (SH), J5.8 (SH), J5.9 (SH), J5.10 (SH), J5.11 (SH), J6.5 (GND), J6.6 (SH), J6.7 (SH), J6.8 (SH), J6.9 (SH), J6.10 (SH), J6.11 (SH), J7.6 (VSS), J7.11 (SHIELD), J8.2, J9.2, J10.2, J11.2, J12.2, J13.2, M1.1 (GND), M1.4 (GND), M1.7 (GND), M1.10 (GND), M1.13 (GND), M1.16 (GND), M1.21 (GND), M1.24 (GND), M1.27 (GND), M1.30 (GND), M1.33 (GND), M1.34 (GND), M1.37 (GND), M1.40 (GND), M1.45 (GND), M1.48 (GND), M1.51 (GND), M1.54 (GND), M1.57 (GND), M1.60 (GND), M1.63 (GND), M1.66 (GND), M1.69 (GND), M1.72 (GND), M1.75 (GND), M1.78 (GND), M1.81 (GND), M1.84 (GND), M1.87 (GND), M1.90 (GND), M1.93 (GND), M1.96 (GND), M1.99 (GND), M1.100 (GND), M1.103 (GND), M1.106 (GND), M1.109 (GND), M1.112 (GND), M1.115 (GND), M1.123 (GND), M1.126 (GND), M1.129 (GND), M1.132 (GND)

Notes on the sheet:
40Way GPIO Header
Fit Jumper to force USB boot
USB
PWR
CSI Camera
CM0Lite SDCARD I/F
Not Fitted headers
DSI Display

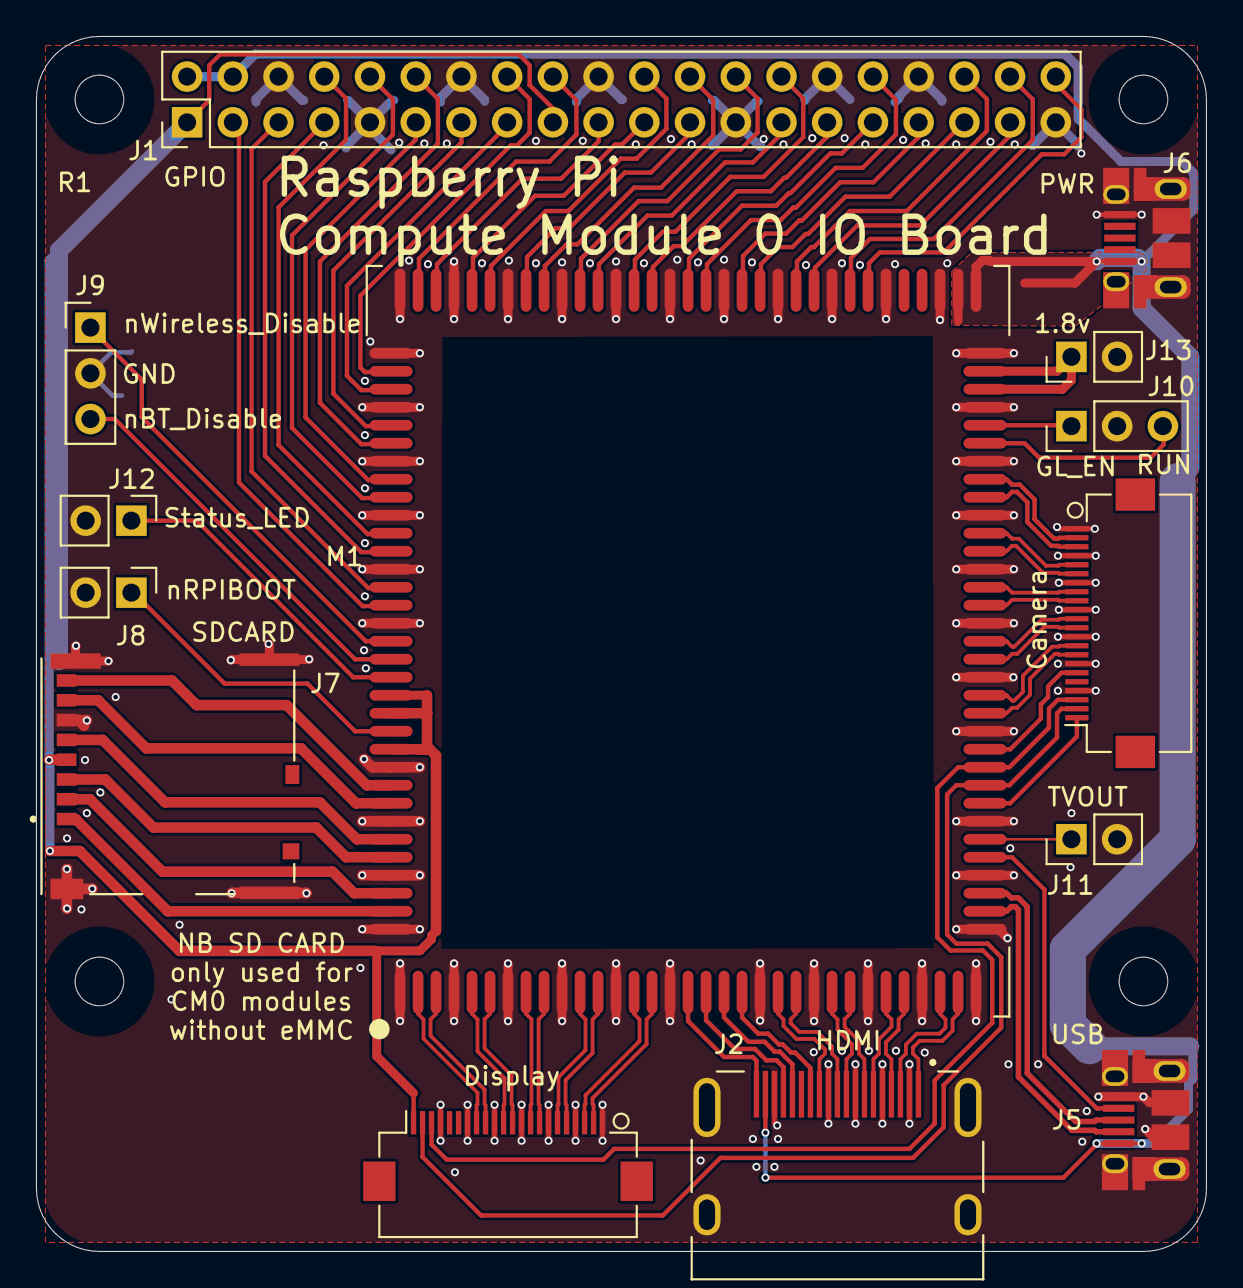
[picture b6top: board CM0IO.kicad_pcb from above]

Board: 2 copper layers, 65.0 x 67.5 mm, 18 parts (0 on the bottom side), 84 nets.
